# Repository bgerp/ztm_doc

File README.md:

# Zontromat - Zonal Electronic Automation

## Introduction

This repository is made to hold all the schematics and sheets around the Zontromat project and BCVT.
This includes:
 - Electrical schematics and sheets.
 - Electronic schematics and sheets.
 - Thermal and hydro schematics and sheets.
 - Flows, diagrams, and charts of the process control.

 This repository is not licensed by single license. Every single project in it is licensed separately, as separate material.

## Limitations

- Every project described in this repository have its own license and terms of use, reproduce, distribution and redistribution.

## Contribution

- Contribution is permitted by the owner of the project by request from the contributor.

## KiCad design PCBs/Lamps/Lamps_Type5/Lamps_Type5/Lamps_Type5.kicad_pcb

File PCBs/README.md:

## Introduction

This folder is made to hold all the schematics and sheets dedicated to electronic equipment and PCBs part of the project Zontromat.

## Contribution

- Contribution is permitted by the owner of the project by request from the contributor.

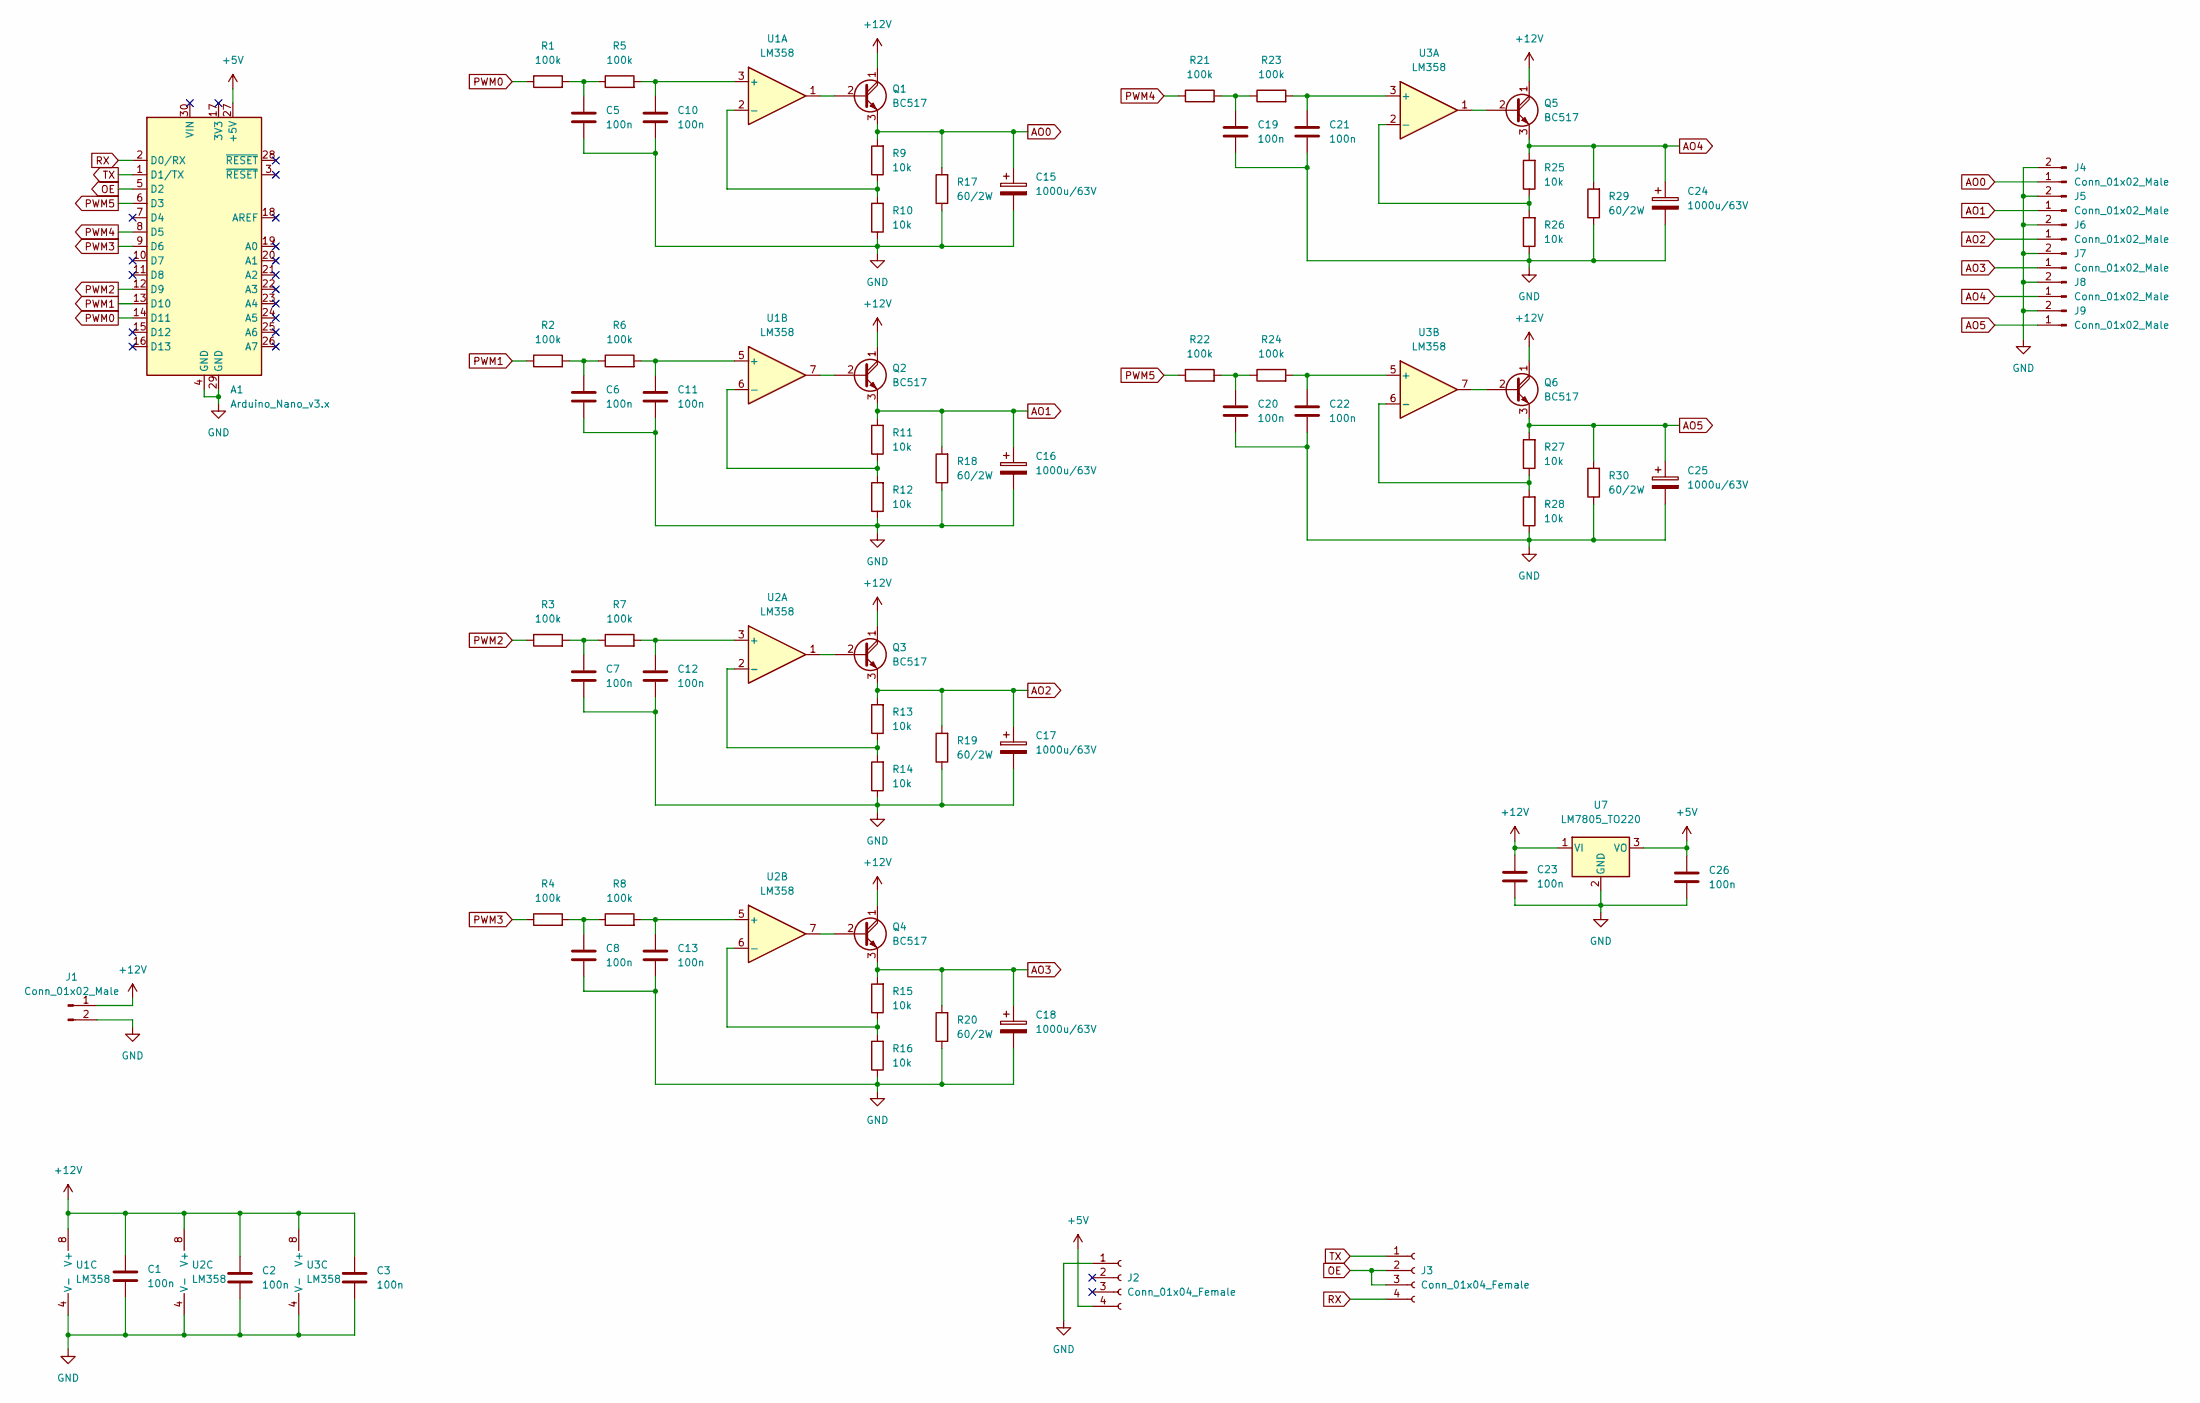
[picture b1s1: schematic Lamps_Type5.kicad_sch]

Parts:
A1: Arduino_Nano_v3.x; Arduino_Nano
C1, C2, C3, C5, C6, C7, C8, C10, C11, C12, C13, C19, C20, C21, C22, C23, C26: 100n; C_Disc_D7.0mm_W2.5mm_P5.00mm
C15, C16, C17, C18, C24, C25: 1000u/63V; C_Radial_D16.0mm_H25.0mm_P7.50mm
J1, J4, J5, J6, J7, J8, J9: Conn_01x02_Male; PhoenixContact_MSTBA_2,5_2-G-5,08_1x02_P5.08mm_Horizontal
J2, J3: Conn_01x04_Female; PinHeader_1x04_P2.54mm_Vertical
Q1, Q2, Q3, Q4, Q5, Q6: BC517; TO-92_Inline
R1, R2, R3, R4, R5, R6, R7, R8, R21, R22, R23, R24: 100k; R_Axial_DIN0204_L3.6mm_D1.6mm_P7.62mm_Horizontal
R9, R10, R11, R12, R13, R14, R15, R16, R25, R26, R27, R28: 10k; R_Axial_DIN0204_L3.6mm_D1.6mm_P7.62mm_Horizontal
R17, R18, R19, R20, R29, R30: 60/2W; R_Axial_DIN0516_L15.5mm_D5.0mm_P7.62mm_Vertical
U1, U2, U3: LM358; DIP-8_W7.62mm
U7: LM7805_TO220; TO-220-3_Vertical

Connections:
+5V: A1.27 (+5V), C26.1, J2.4, U7.3 (VO)
+12V: C1.1, C2.1, C3.1, C23.1, J1.1, Q1.1 (C), Q2.1 (C), Q3.1 (C), Q4.1 (C), Q5.1 (C), Q6.1 (C), U1.8 (V+), U2.8 (V+), U3.8 (V+), U7.1 (VI); also elsewhere on the board
AO0: C15.1, J4.1, Q1.3 (E), R9.2, R17.2
AO1: C16.1, J5.1, Q2.3 (E), R11.2, R18.2
AO2: C17.1, J6.1, Q3.3 (E), R13.2, R19.2
AO3: C18.1, J7.1, Q4.3 (E), R15.2, R20.2
AO4: C24.1, J8.1, Q5.3 (E), R25.2, R29.2
AO5: C25.1, J9.1, Q6.3 (E), R27.2, R30.2
GND: A1.4 (GND), A1.29 (GND), C1.2, C2.2, C3.2, C5.2, C6.2, C7.2, C8.2, C10.2, C11.2, C12.2, C13.2, C15.2, C16.2, C17.2, C18.2, C19.2, C20.2, C21.2, C22.2, C23.2, C24.2, C25.2, C26.2, J1.2, J2.1, J4.2, J5.2, J6.2, J7.2, J8.2, J9.2, R10.1, R12.1, R14.1, R16.1, R17.1, R18.1, R19.1, R20.1, R26.1, R28.1, R29.1, R30.1, U1.4 (V-), U2.4 (V-), U3.4 (V-), U7.2 (GND); also elsewhere on the board
unnamed: C5.1, R1.2, R5.1
unnamed: C6.1, R2.2, R6.1
unnamed: C7.1, R3.2, R7.1
unnamed: C8.1, R4.2, R8.1
unnamed: C10.1, R5.2, U1.3 (+)
unnamed: C11.1, R6.2, U1.5 (+)
unnamed: C12.1, R7.2, U2.3 (+)
unnamed: C13.1, R8.2, U2.5 (+)
unnamed: C19.1, R21.2, R23.1
unnamed: C20.1, R22.2, R24.1
unnamed: C21.1, R23.2, U3.3 (+)
unnamed: C22.1, R24.2, U3.5 (+)
unnamed: Q1.2 (B), U1.1
unnamed: Q2.2 (B), U1.7
unnamed: Q3.2 (B), U2.1
unnamed: Q4.2 (B), U2.7
unnamed: Q5.2 (B), U3.1
unnamed: Q6.2 (B), U3.7
unnamed: R9.1, R10.2, U1.2 (-)
unnamed: R11.1, R12.2, U1.6 (-)
unnamed: R13.1, R14.2, U2.2 (-)
unnamed: R15.1, R16.2, U2.6 (-)
unnamed: R25.1, R26.2, U3.2 (-)
unnamed: R27.1, R28.2, U3.6 (-)
OE: A1.5 (D2), J3.2, J3.3
PWM0: A1.14 (D11), R1.1
PWM1: A1.13 (D10), R2.1
PWM2: A1.12 (D9), R3.1
PWM3: A1.9 (D6), R4.1
PWM4: A1.8 (D5), R21.1
PWM5: A1.6 (D3), R22.1
RX: A1.2 (D0/RX), J3.4
TX: A1.1 (D1/TX), J3.1

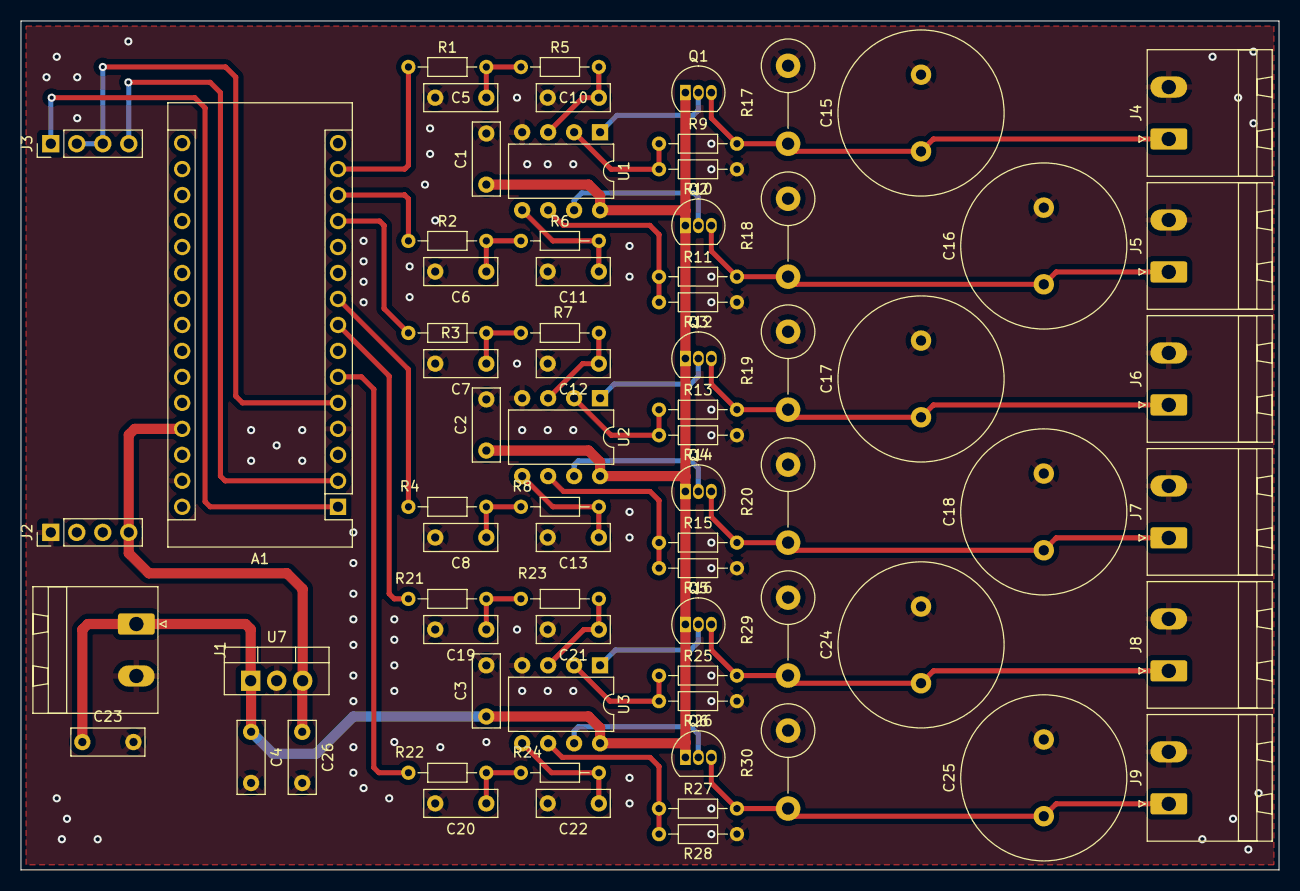
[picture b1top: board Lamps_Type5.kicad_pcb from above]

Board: 2 copper layers, 123.0 x 83.0 mm, 74 parts (0 on the bottom side), 42 nets.

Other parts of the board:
C4: 100n; C_Disc_D7.0mm_W2.5mm_P5.00mm

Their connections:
+12V: C4.1; also elsewhere on the board
GND: C4.2; also elsewhere on the board

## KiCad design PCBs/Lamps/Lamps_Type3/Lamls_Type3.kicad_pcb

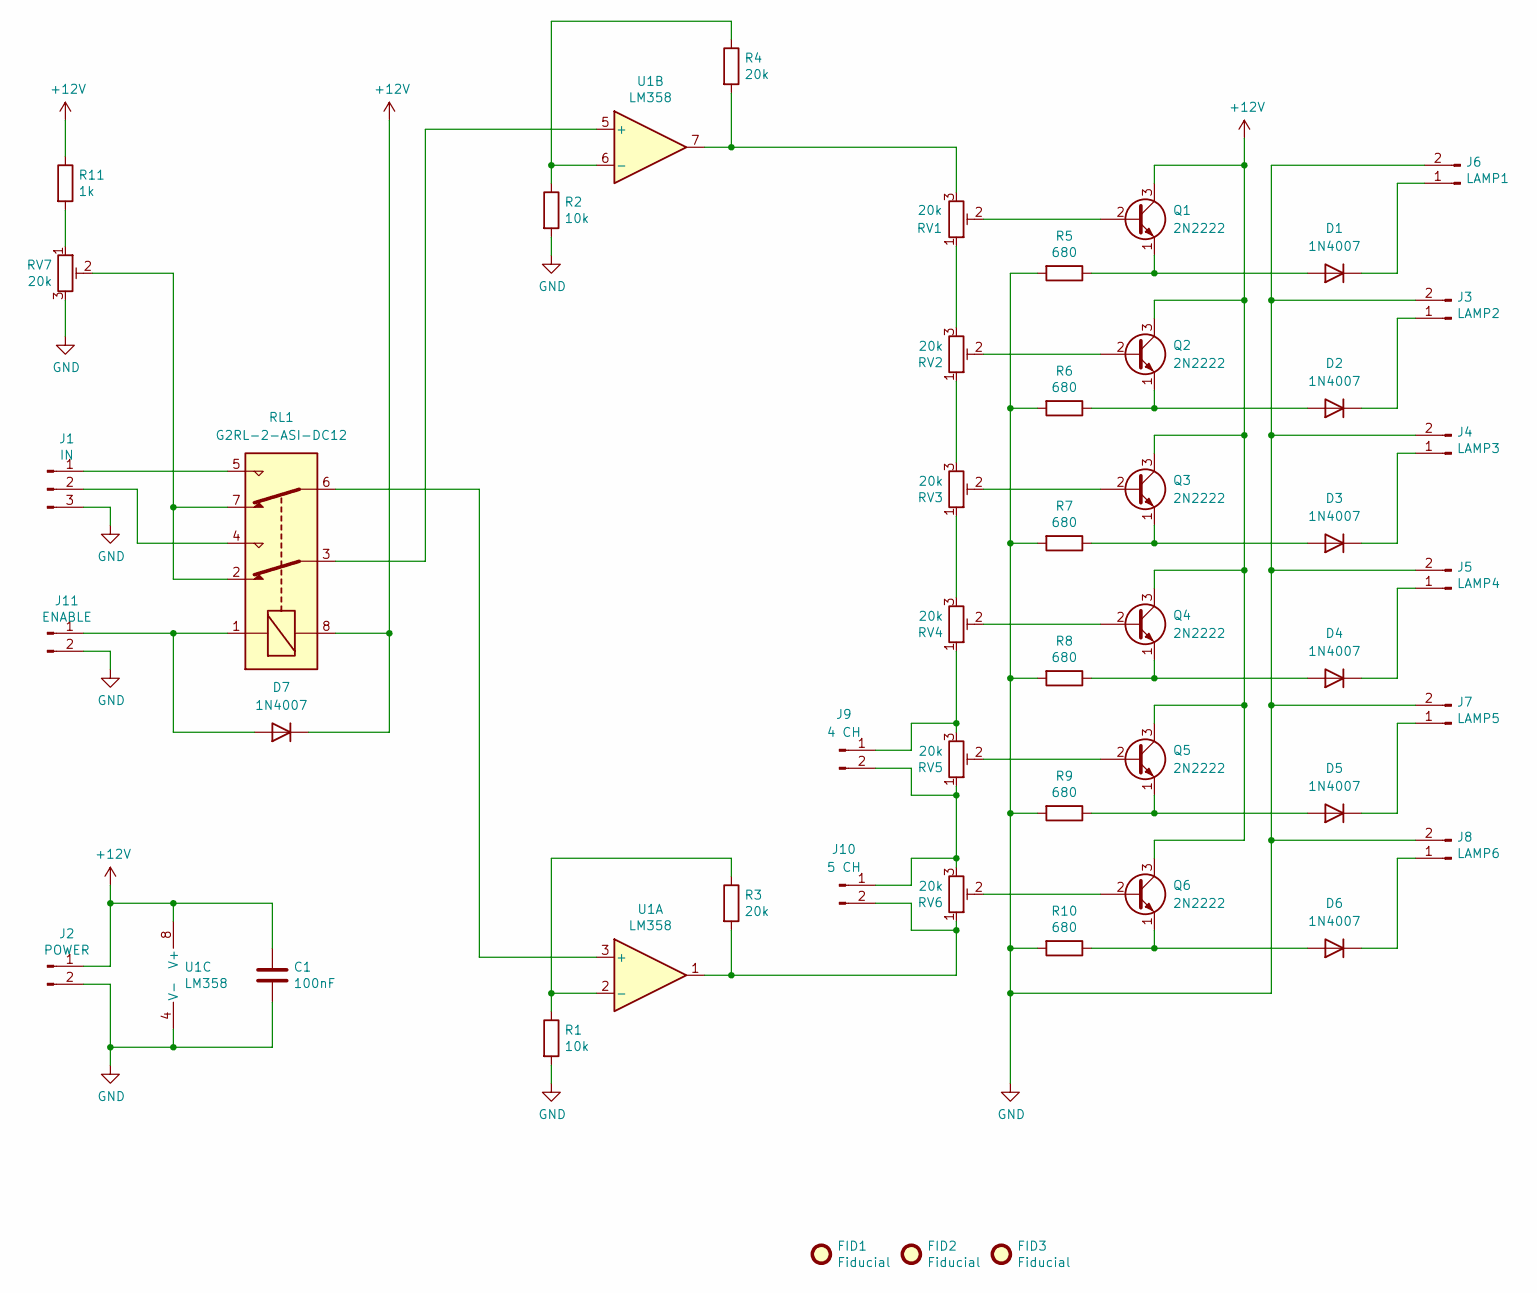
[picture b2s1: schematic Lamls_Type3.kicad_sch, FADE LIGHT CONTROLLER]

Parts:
C1: 100nF; C_0805_2012Metric
D1, D2, D3, D4, D5, D6, D7: 1N4007; D_SMA
FID1, FID2, FID3: Fiducial; Fiducial_0.5mm_Mask1.5mm
J1: IN; TerminalBlock_Phoenix_MKDS-1,5-3_1x03_P5.00mm_Horizontal
J2: POWER; TerminalBlock_Phoenix_MKDS-1,5-2_1x02_P5.00mm_Horizontal
J3: LAMP2; TerminalBlock_Phoenix_MKDS-1,5-2_1x02_P5.00mm_Horizontal
J4: LAMP3; TerminalBlock_Phoenix_MKDS-1,5-2_1x02_P5.00mm_Horizontal
J5: LAMP4; TerminalBlock_Phoenix_MKDS-1,5-2_1x02_P5.00mm_Horizontal
J6: LAMP1; TerminalBlock_Phoenix_MKDS-1,5-2_1x02_P5.00mm_Horizontal
J7: LAMP5; TerminalBlock_Phoenix_MKDS-1,5-2_1x02_P5.00mm_Horizontal
J8: LAMP6; TerminalBlock_Phoenix_MKDS-1,5-2_1x02_P5.00mm_Horizontal
J9: 4 CH; PinHeader_1x02_P2.54mm_Vertical
J10: 5 CH; PinHeader_1x02_P2.54mm_Vertical
J11: ENABLE; TerminalBlock_Phoenix_MKDS-1,5-2_1x02_P5.00mm_Horizontal
Q1, Q2, Q3, Q4, Q5, Q6: 2N2222; TO-92_Inline_Wide
R1, R2: 10k; R_0805_2012Metric
R3, R4: 20k; R_0805_2012Metric
R5, R6, R7, R8, R9, R10: 680; R_0805_2012Metric
R11: 1k; R_0805_2012Metric
RL1: G2RL-2-ASI-DC12; Relay_DPDT_Omron_G2RL
RV1, RV2, RV3, RV4, RV5, RV6, RV7: 20k; Potentiometer_ACP_CA9-V10_Vertical
U1: LM358; SO-8_5.3x6.2mm_P1.27mm

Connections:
+12V: C1.1, D7.1 (K), J2.1, Q1.3 (C), Q2.3 (C), Q3.3 (C), Q4.3 (C), Q5.3 (C), Q6.3 (C), R11.1, RL1.8, U1.8 (V+)
GND: C1.2, J1.3, J2.2, J3.2, J4.2, J5.2, J6.2, J7.2, J8.2, J11.2, R1.2, R2.2, R5.2, R6.2, R7.2, R8.2, R9.2, R10.2, RV7.3, U1.4 (V-)
unnamed: D1.2 (A), Q1.1 (E), R5.1
unnamed: D2.2 (A), Q2.1 (E), R6.1
unnamed: D3.2 (A), Q3.1 (E), R7.1
unnamed: D4.2 (A), Q4.1 (E), R8.1
unnamed: D5.2 (A), Q5.1 (E), R9.1
unnamed: D6.2 (A), Q6.1 (E), R10.1
unnamed: D2.1 (K), J3.1
unnamed: D3.1 (K), J4.1
unnamed: D4.1 (K), J5.1
unnamed: D1.1 (K), J6.1
unnamed: D5.1 (K), J7.1
unnamed: D6.1 (K), J8.1
unnamed: J9.1, RV4.1, RV5.3
unnamed: J9.2, J10.1, RV5.1, RV6.3
unnamed: J10.2, R3.2, RV6.1, U1.1
unnamed: Q1.2 (B), RV1.2
unnamed: Q2.2 (B), RV2.2
unnamed: Q3.2 (B), RV3.2
unnamed: Q4.2 (B), RV4.2
unnamed: Q5.2 (B), RV5.2
unnamed: Q6.2 (B), RV6.2
unnamed: R1.1, R3.1, U1.2 (-)
unnamed: R2.1, R4.1, U1.6 (-)
unnamed: R11.2, RV7.1
unnamed: D7.2 (A), J11.1, RL1.1
unnamed: RL1.2, RL1.7, RV7.2
unnamed: RL1.3, U1.5 (+)
unnamed: J1.2, RL1.4
unnamed: J1.1, RL1.5
unnamed: RL1.6, U1.3 (+)
unnamed: RV1.1, RV2.3
unnamed: R4.2, RV1.3, U1.7
unnamed: RV2.1, RV3.3
unnamed: RV3.1, RV4.3

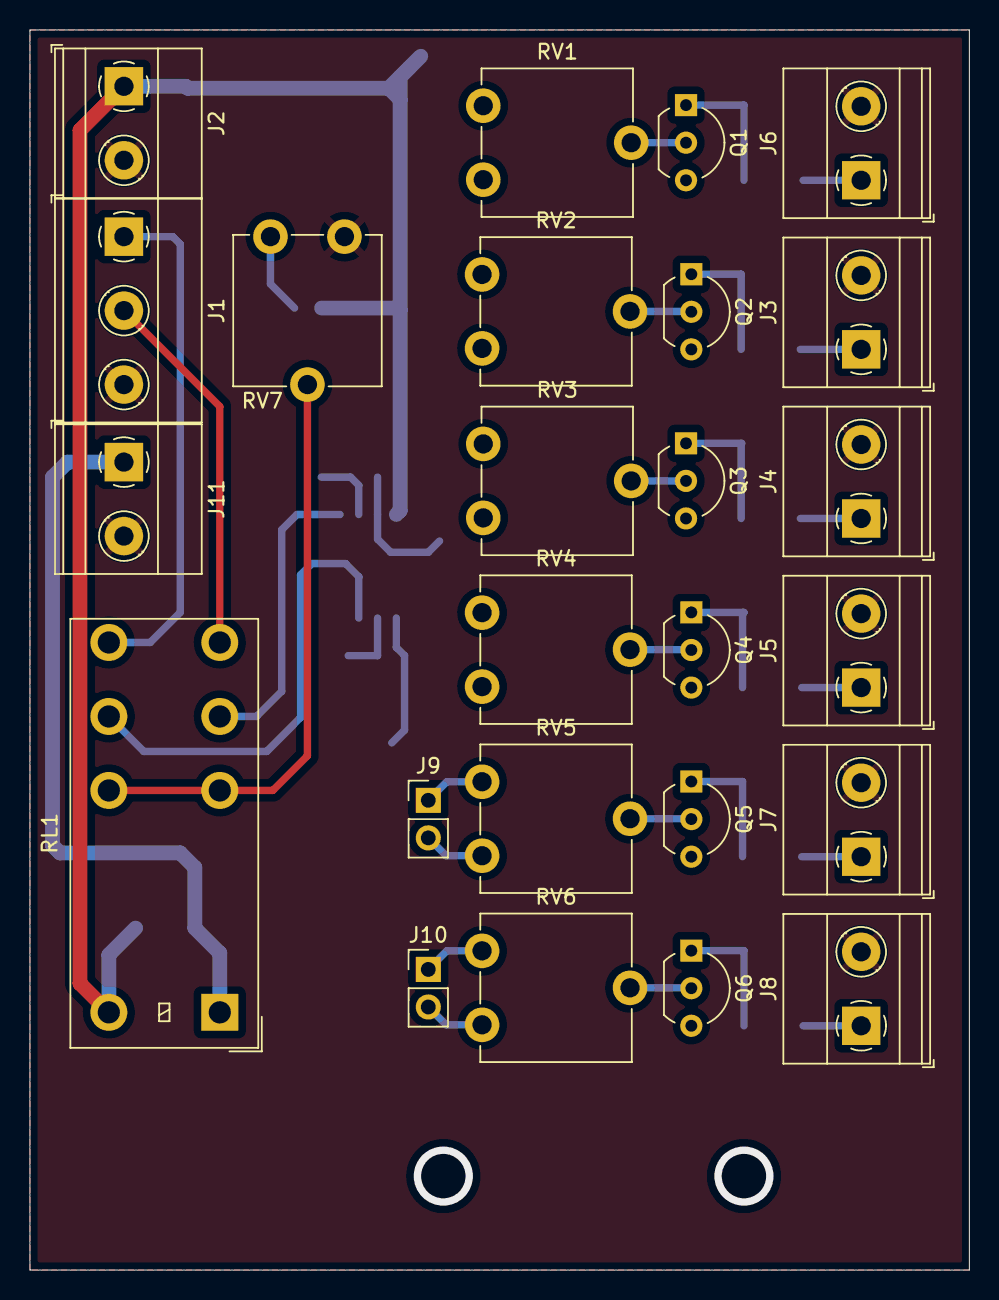
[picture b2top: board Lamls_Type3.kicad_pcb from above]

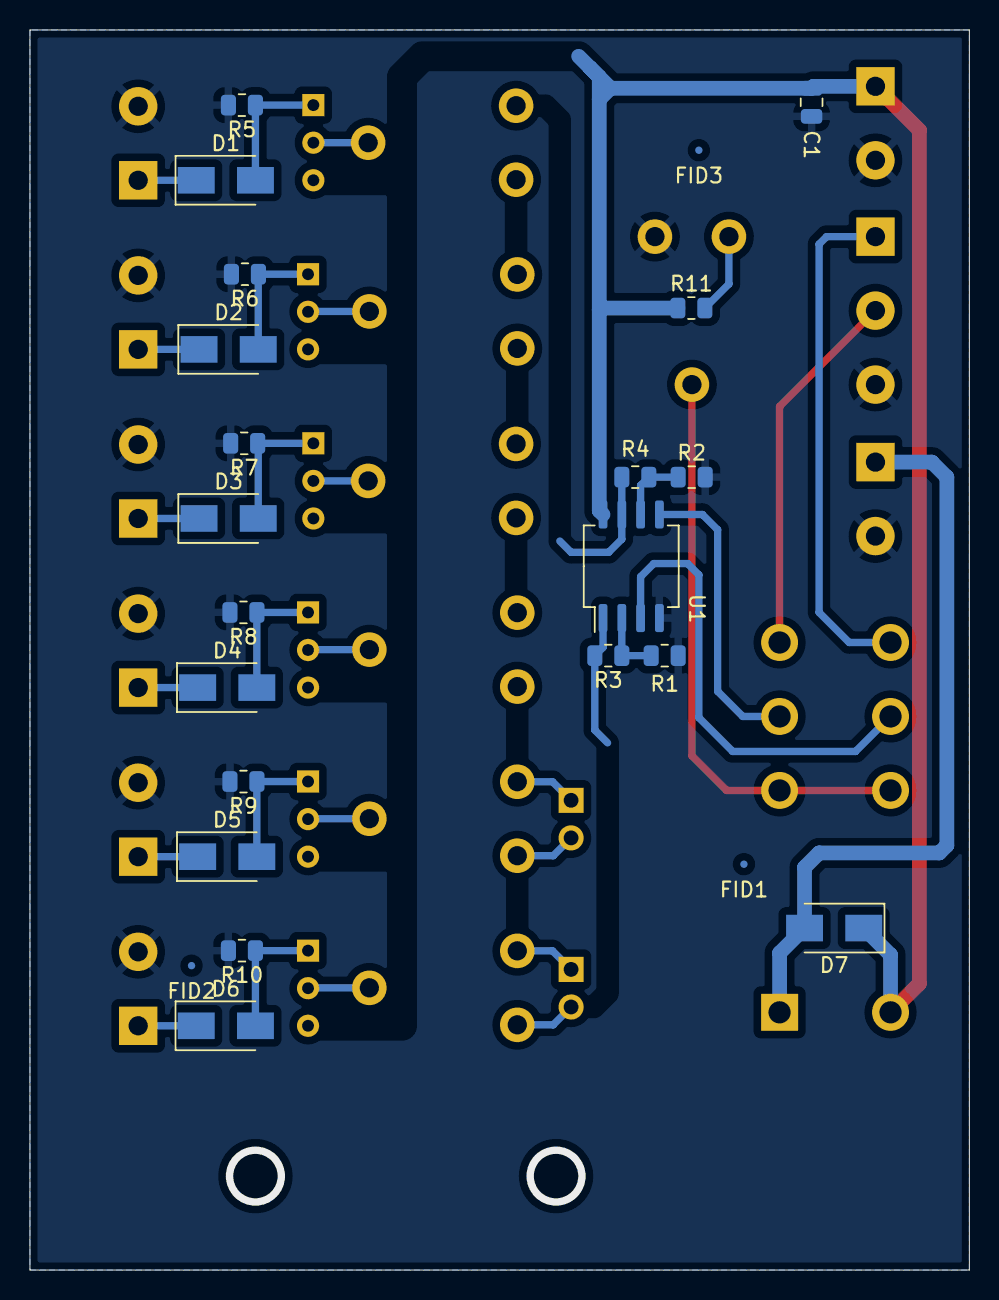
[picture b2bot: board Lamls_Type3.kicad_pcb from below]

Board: 2 copper layers, 63.5 x 83.8 mm, 48 parts (23 on the bottom side), 36 nets.

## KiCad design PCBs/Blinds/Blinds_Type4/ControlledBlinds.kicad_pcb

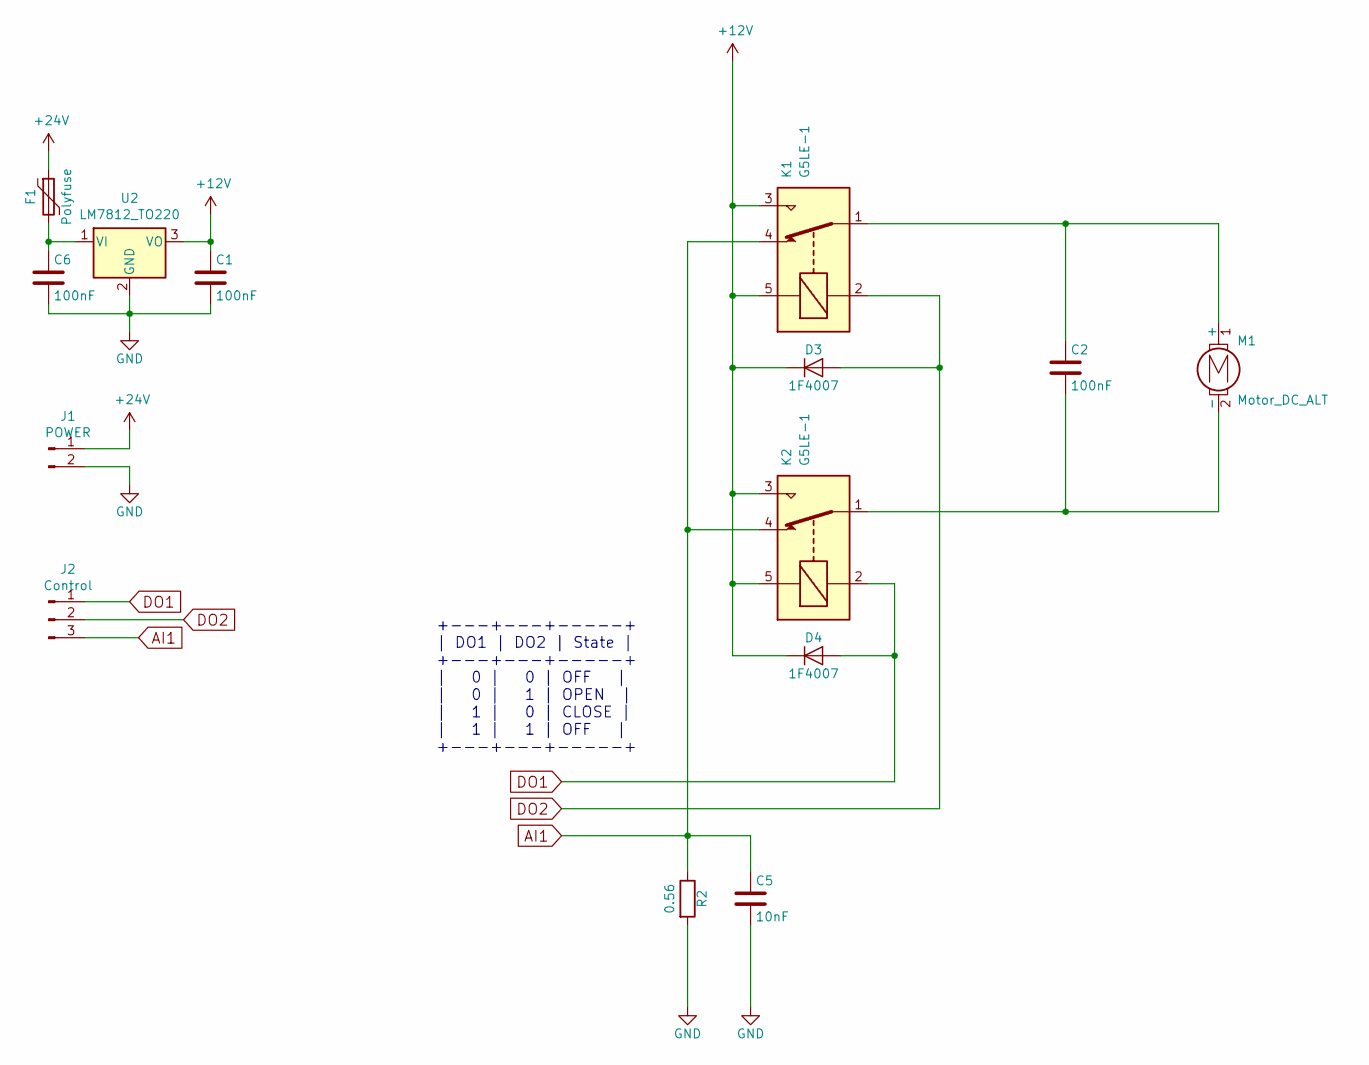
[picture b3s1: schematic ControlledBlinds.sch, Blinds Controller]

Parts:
C1, C2, C6: 100nF; C_0805_2012Metric
C5: 10nF; C_0805_2012Metric
D3, D4: 1F4007; D_SMA
F1: Polyfuse; Fuseholder_TR5_Littelfuse_No560_No460
J1: POWER; PhoenixContact_MSTBA_2,5_2-G_1x02_P5.00mm_Horizontal
J2: Control; PhoenixContact_MSTBA_2,5_3-G-5,08_1x03_P5.08mm_Horizontal
K1, K2: G5LE-1; Relay_SPDT_Omron-G5LE-1
M1: Motor_DC_ALT; PhoenixContact_MSTBA_2,5_2-G-5,08_1x02_P5.08mm_Horizontal
R2: 0.56; R_Axial_Power_L25.0mm_W6.4mm_P27.94mm
U2: LM7812_TO220; TO-220-3_Horizontal_TabDown

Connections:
+12V: C1.1, D3.1 (K), D4.1 (K), K1.3, K1.5, K2.3, K2.5, U2.3 (VO)
+24V: F1.1, J1.1
AI1: C5.1, J2.3, K1.4, K2.4, R2.1
DO1: D4.2 (A), J2.1, K2.2
DO2: D3.2 (A), J2.2, K1.2
GND: C1.2, C5.2, C6.2, J1.2, R2.2, U2.2 (GND)
unnamed: C2.1, K1.1, M1.1 (+)
unnamed: C2.2, K2.1, M1.2 (-)
unnamed: C6.1, F1.2, U2.1 (VI)

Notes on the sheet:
+---+---+-----+ | DO1 | DO2 | State | +---+---+-----+ | 0 | 0 | OFF | | 0 | 1 | OPEN | | 1 | 0 | CLOSE | | 1 | 1 | OFF | +---+---+-----+

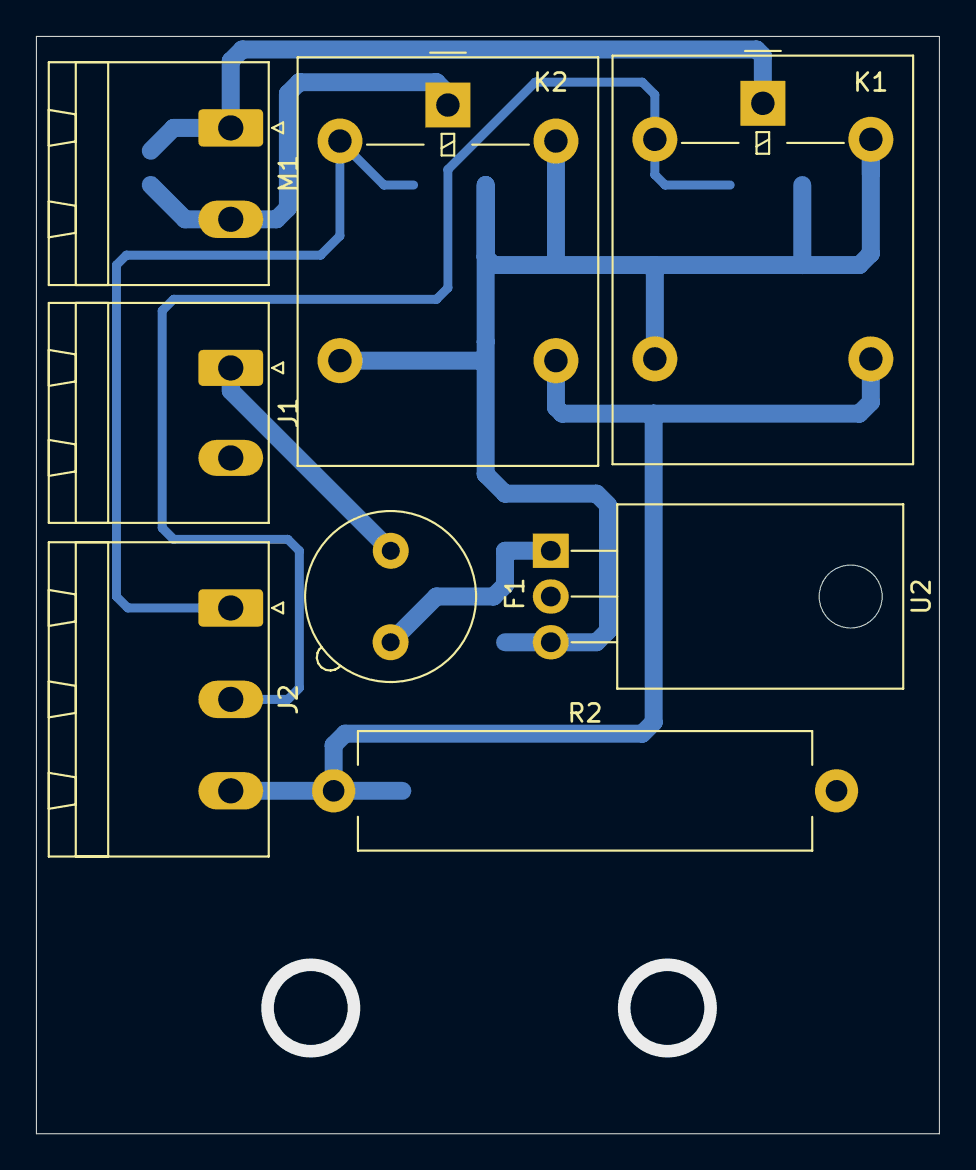
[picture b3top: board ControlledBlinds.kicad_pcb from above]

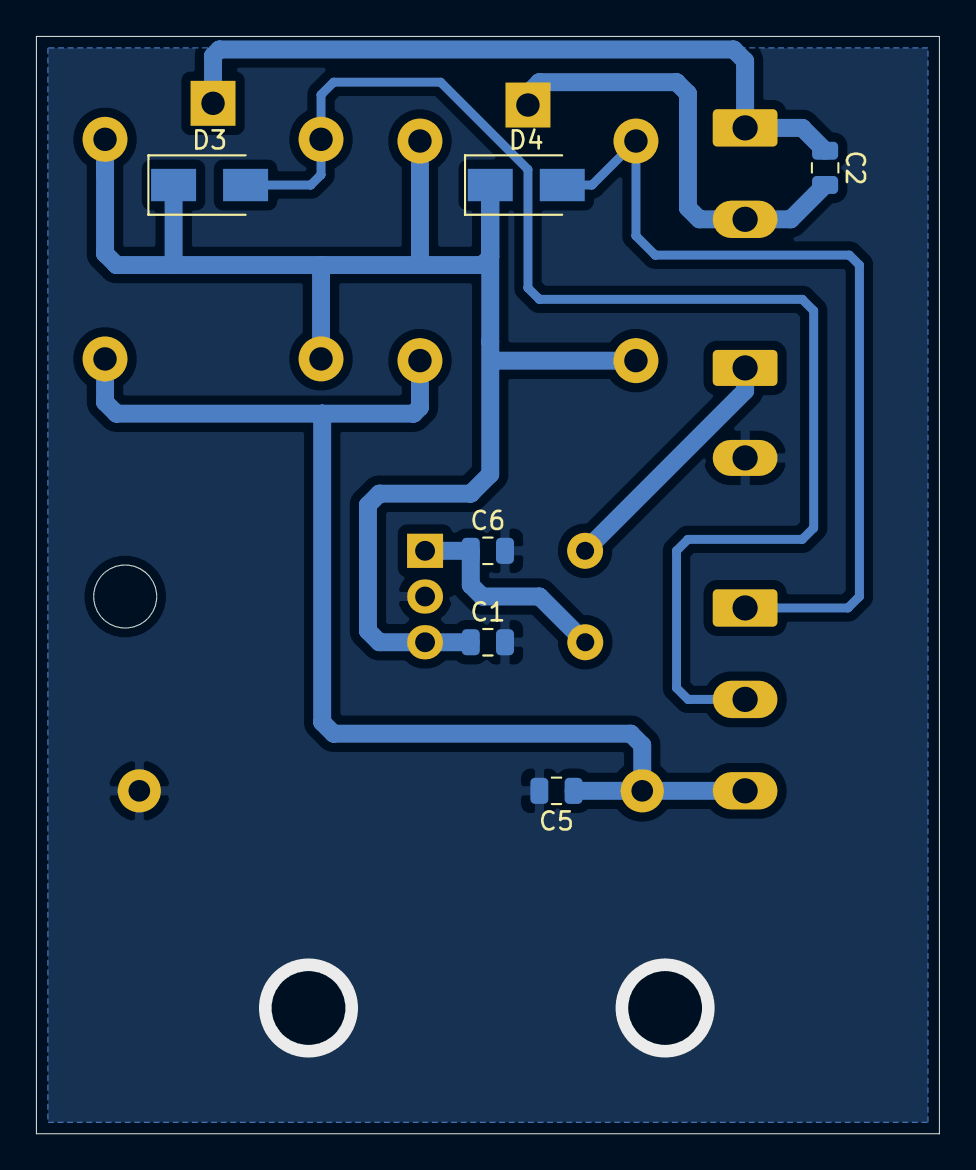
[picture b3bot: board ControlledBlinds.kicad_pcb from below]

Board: 2 copper layers, 50.2 x 61.0 mm, 14 parts (6 on the bottom side), 9 nets.

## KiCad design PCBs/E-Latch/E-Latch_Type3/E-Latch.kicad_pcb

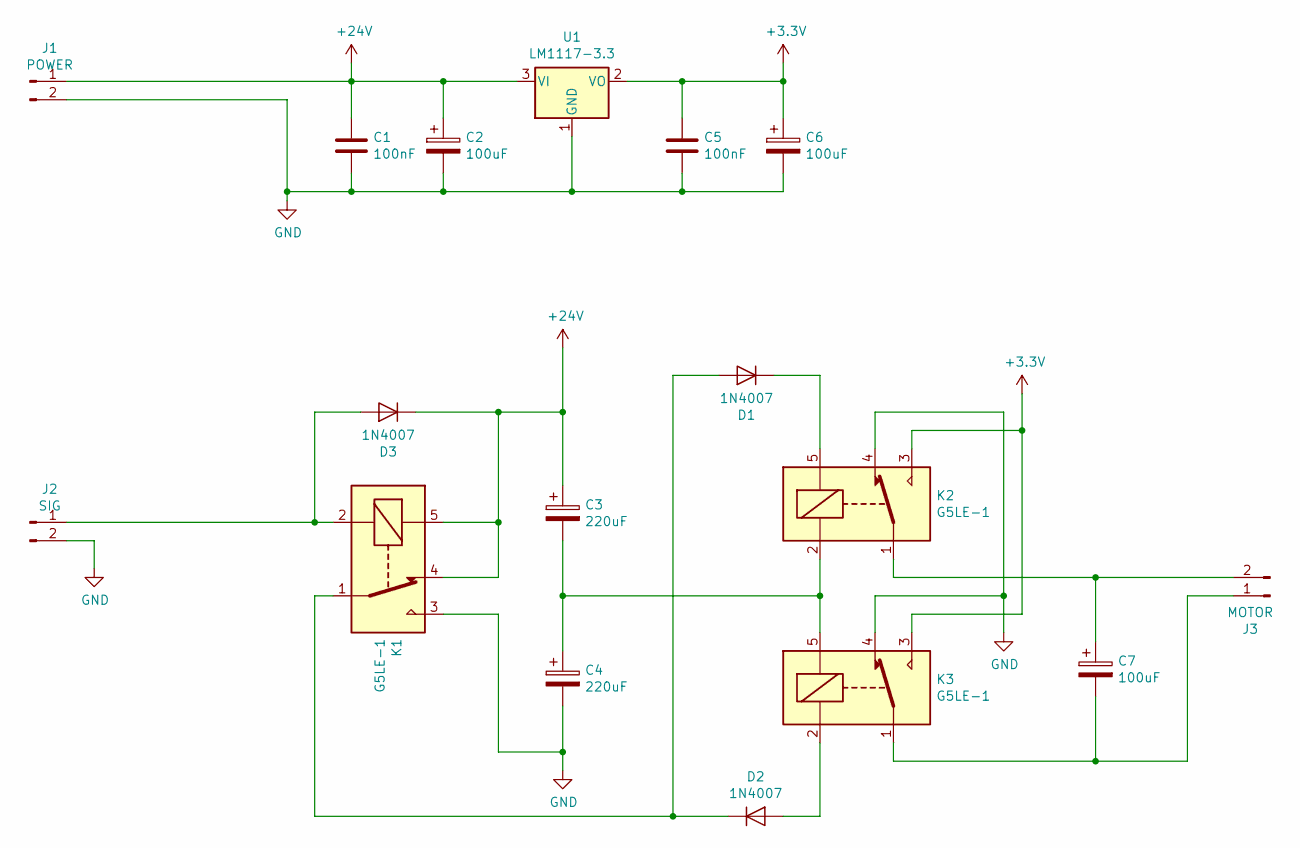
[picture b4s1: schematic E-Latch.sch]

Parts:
C1, C5: 100nF; C_0805_2012Metric
C2, C6: 100uF; CP_Radial_D8.0mm_P3.50mm
C3, C4: 220uF; CP_Radial_D8.0mm_P3.50mm
C7: 100uF; C_0805_2012Metric
D1, D2, D3: 1N4007; D_SMA
J1: POWER; PhoenixContact_MSTBVA_2,5_2-G-5,08_1x02_P5.08mm_Vertical
J2: SIG; PhoenixContact_MSTBVA_2,5_2-G-5,08_1x02_P5.08mm_Vertical
J3: MOTOR; PhoenixContact_MSTBVA_2,5_2-G-5,08_1x02_P5.08mm_Vertical
K1, K2, K3: G5LE-1; Relay_SPDT_Omron-G5LE-1
U1: LM1117-3.3; SOT-89-3_Handsoldering

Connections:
+3V3: C5.1, C6.1, K2.3, K3.3, U1.2 (VO)
+24V: C1.1, C2.1, C3.1, D3.1 (K), J1.1, K1.4, K1.5, U1.3 (VI)
GND: C1.2, C2.2, C4.2, C5.2, C6.2, J1.2, J2.2, K1.3, K2.4, K3.4, U1.1 (GND)
unnamed: C3.2, C4.1, K2.2, K3.5
unnamed: C7.1, J3.2, K2.1
unnamed: C7.2, J3.1, K3.1
unnamed: D1.1 (K), K2.5
unnamed: D1.2 (A), D2.1 (K), K1.1
unnamed: D2.2 (A), K3.2
unnamed: D3.2 (A), J2.1, K1.2

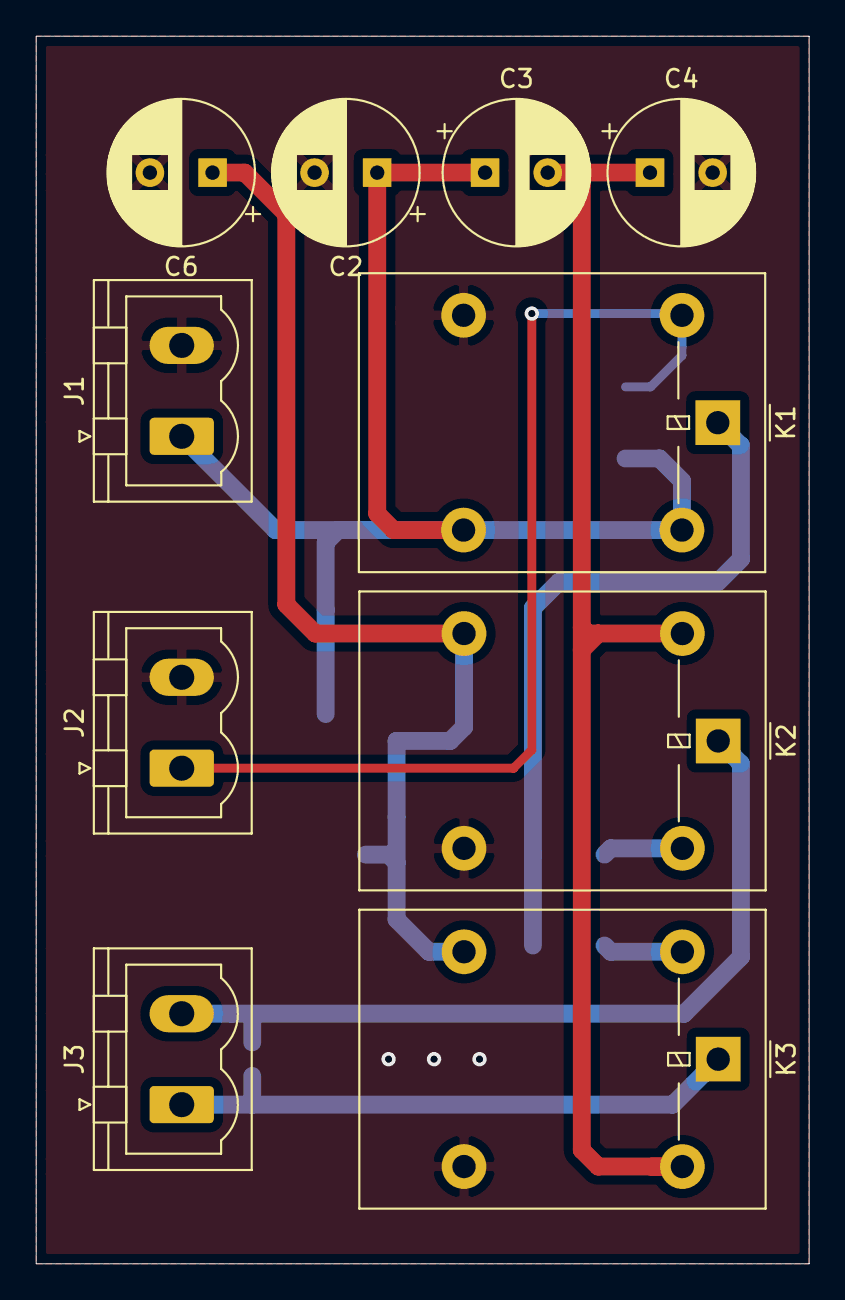
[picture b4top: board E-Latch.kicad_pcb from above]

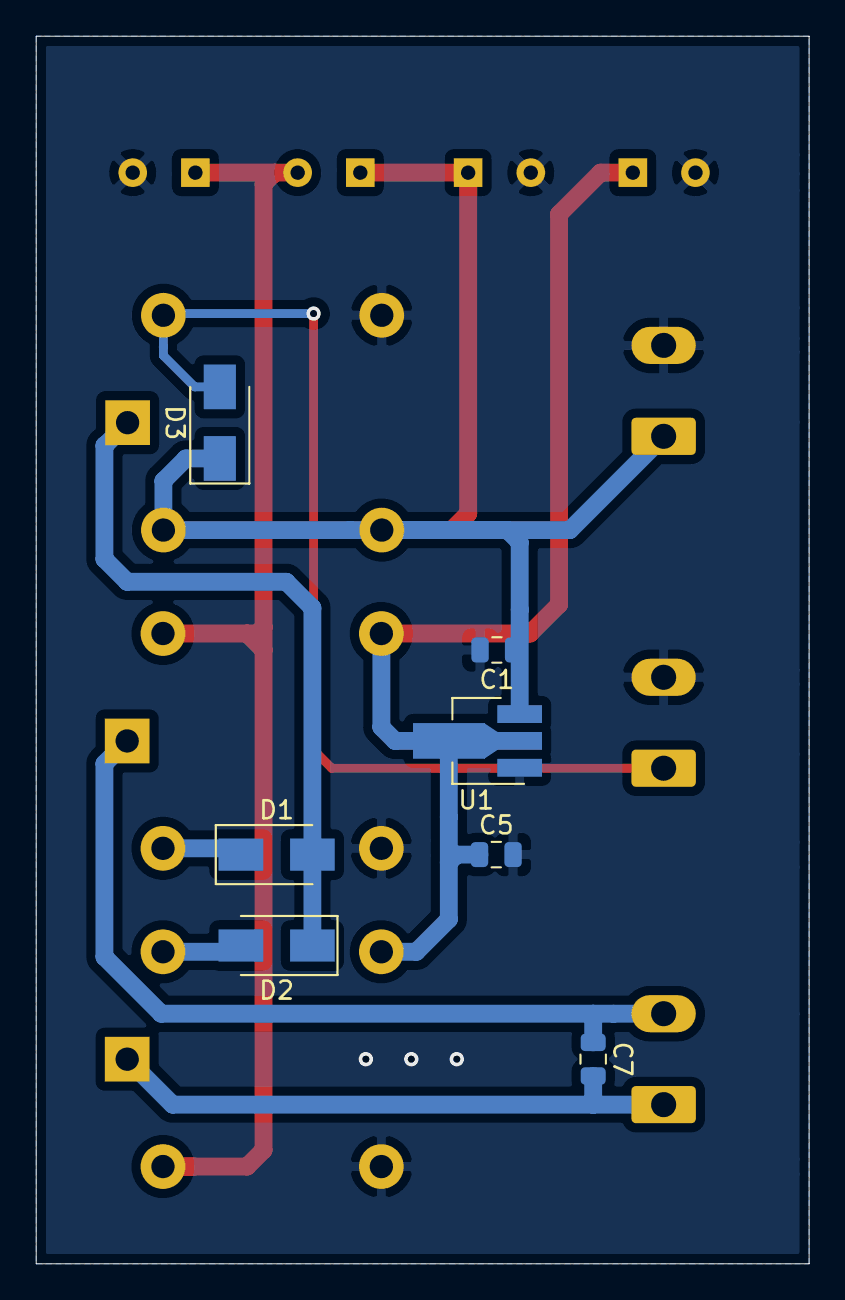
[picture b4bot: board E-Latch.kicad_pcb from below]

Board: 2 copper layers, 43.2 x 68.6 mm, 17 parts (7 on the bottom side), 10 nets.

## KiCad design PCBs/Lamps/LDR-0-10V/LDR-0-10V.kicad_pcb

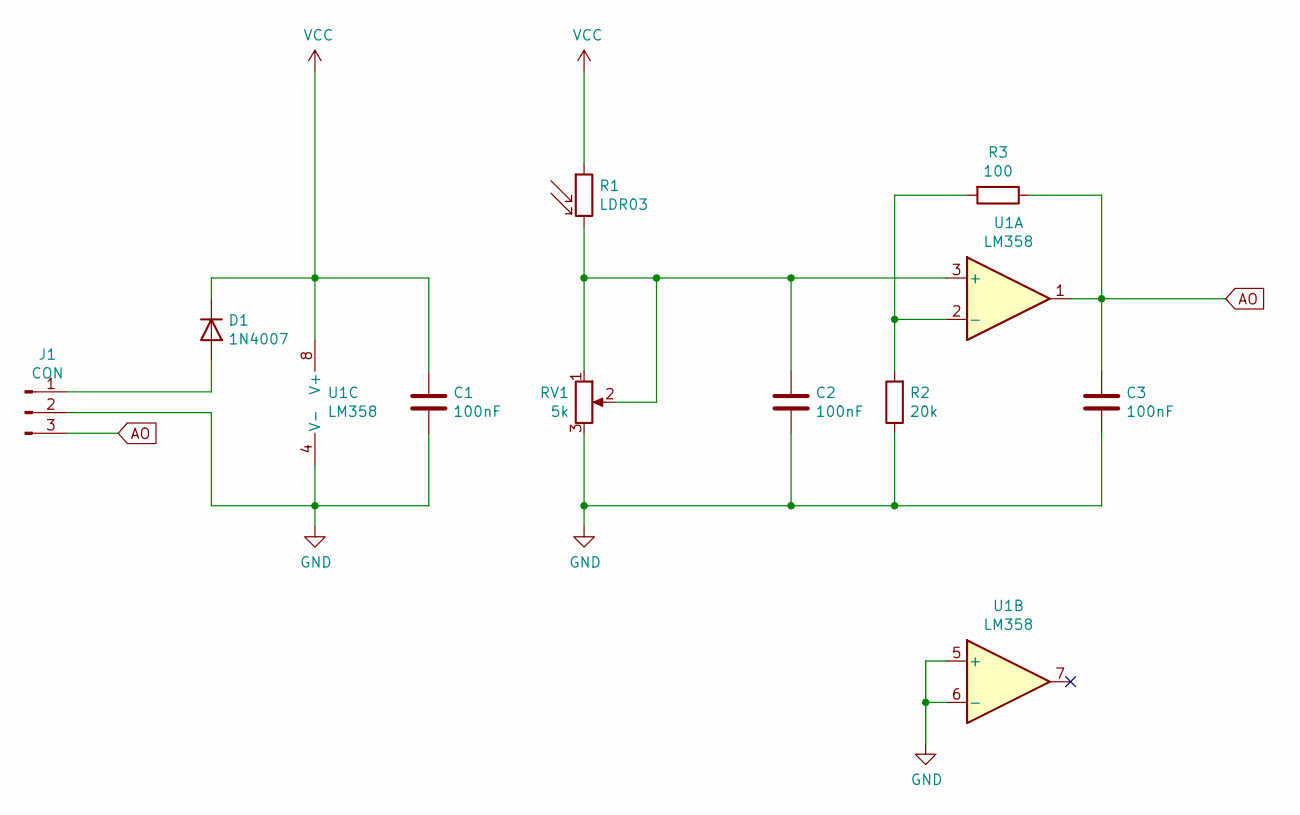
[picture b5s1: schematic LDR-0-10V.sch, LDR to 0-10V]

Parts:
C1, C2, C3: 100nF; C_Disc_D7.0mm_W2.5mm_P5.00mm
D1: 1N4007; D_DO-41_SOD81_P10.16mm_Horizontal
J1: CON; PhoenixContact_MSTBA_2,5_3-G-5,08_1x03_P5.08mm_Horizontal
R1: LDR03; R_LDR_5.0x4.1mm_P3mm_Vertical
R2: 20k; R_Axial_DIN0207_L6.3mm_D2.5mm_P10.16mm_Horizontal
R3: 100; R_Axial_DIN0207_L6.3mm_D2.5mm_P10.16mm_Horizontal
RV1: 5k; Potentiometer_ACP_CA9-V10_Vertical_Hole
U1: LM358; DIP-8_W7.62mm_LongPads

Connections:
AO: C3.1, J1.3, R3.1, U1.1
GND: C1.2, C2.2, C3.2, J1.2, R2.1, RV1.3, U1.4 (V-), U1.5 (+), U1.6 (-)
unnamed: C2.1, R1.2, RV1.1, RV1.2, U1.3 (+)
unnamed: D1.2 (A), J1.1
unnamed: R2.2, R3.2, U1.2 (-)
VCC: C1.1, D1.1 (K), R1.1, U1.8 (V+)
